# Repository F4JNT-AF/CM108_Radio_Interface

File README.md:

# [FR] (EN below)
## Description
Une interface basique USB entre une radio et un PC. Rien de révolutionnaire, j'ai essayé de mettre le maximum de composants traversants, avec deux exceptions assez techniques, le CM108 lui-même (pas trop le choix quand on veut faire une interface a base de CM108 :) ) et le connecteur USB-C (très pratique pour connecter en direct au téléphone sans OTG).

Avec cette interface, il est possible de faire de nombreux modes: packet, SSTV, RTTY, Rattlegram (COFDMTV), FT8 ... la seule limite étant ce que votre PC peut faire et la bande passante du transfo audio (il devrait être possible de ponter le transfo pour faire du packet en 9600 bauds sur les radios qui peuvent).

Une EEPROM (93C46B) peut être montée et servir a stocker un nom personnalisé pour l'interface ainsi que des paramètres audio par défaut.

[Objet d'un atelier en Mars 2025 a l'ARA35](https://ara35.fr/ce-soir-la-on-a-fabrique-des-interfaces-modes-numeriques-au-radio-club-f4kio/)

## Pinout connecteur RJ45
Le connecteur vers la radio est un RJ45. Le pinout est:
1. Speaker radio
2. Micro radio
3. PTT
4. GND radio
5. GND radio
6. GND radio
7. GND radio
8. GND radio

## Configuration de l'EEPROM
Utiliser le fichier .cfg (optionnel: mettre un numéro de série) ou .hex avec [mon configurateur d'EEPROM pour CM108B](https://github.com/F4JNT-AF/CM108B_EEPROM_Manager).

## Note
Comme toutes les interfaces de ce type, elle est plutôt sensible aux retours RF, je conseille de mettre des ferrites, au moins sur le câble USB.

73, Axel F4JNT

# [EN]
## Description
A basic USB interface between a radio and a PC. Nothing groundbreaking, I tried to use the maximum number of through-hole components, with two exceptions that are tricky to solder, the CM108 itself (not much choice when your interface is CM108-based :) ) and the USB-C connector (very handy to connect).

With this interface, you can do a lot of modes such as packet, SSTV, RTTY, Rattlegram (COFDMTV), FT8 ... your only limits will be what your PC or phone can handle and the bandwidth of the audio transformer (it should be possible to do 9600 bauds packet on compatible radios by shunting the transformers)

An EEPROM (93C46B) can be populated and may store a custom device name and audio parameters.

[Did a kit + workshop at ARA35](https://ara35.fr/ce-soir-la-on-a-fabrique-des-interfaces-modes-numeriques-au-radio-club-f4kio/)

## RJ45 Pinout
Connector to radio is RJ45. Pinout:
1. Speaker radio
2. Mic radio
3. PTT
4. GND radio
5. GND radio
6. GND radio
7. GND radio
8. GND radio

## EEPROM configuration
Use the .cfg file (optional: put a serial number) or .hex file with [my CM108B EEPROM configurator](https://github.com/F4JNT-AF/CM108B_EEPROM_Manager).

## Note
Note: As all interfaces of this type, it is vulnerable to RF feedback, I'd advise to at least add some ferrites to USB cable.

73, Axel F4JNT

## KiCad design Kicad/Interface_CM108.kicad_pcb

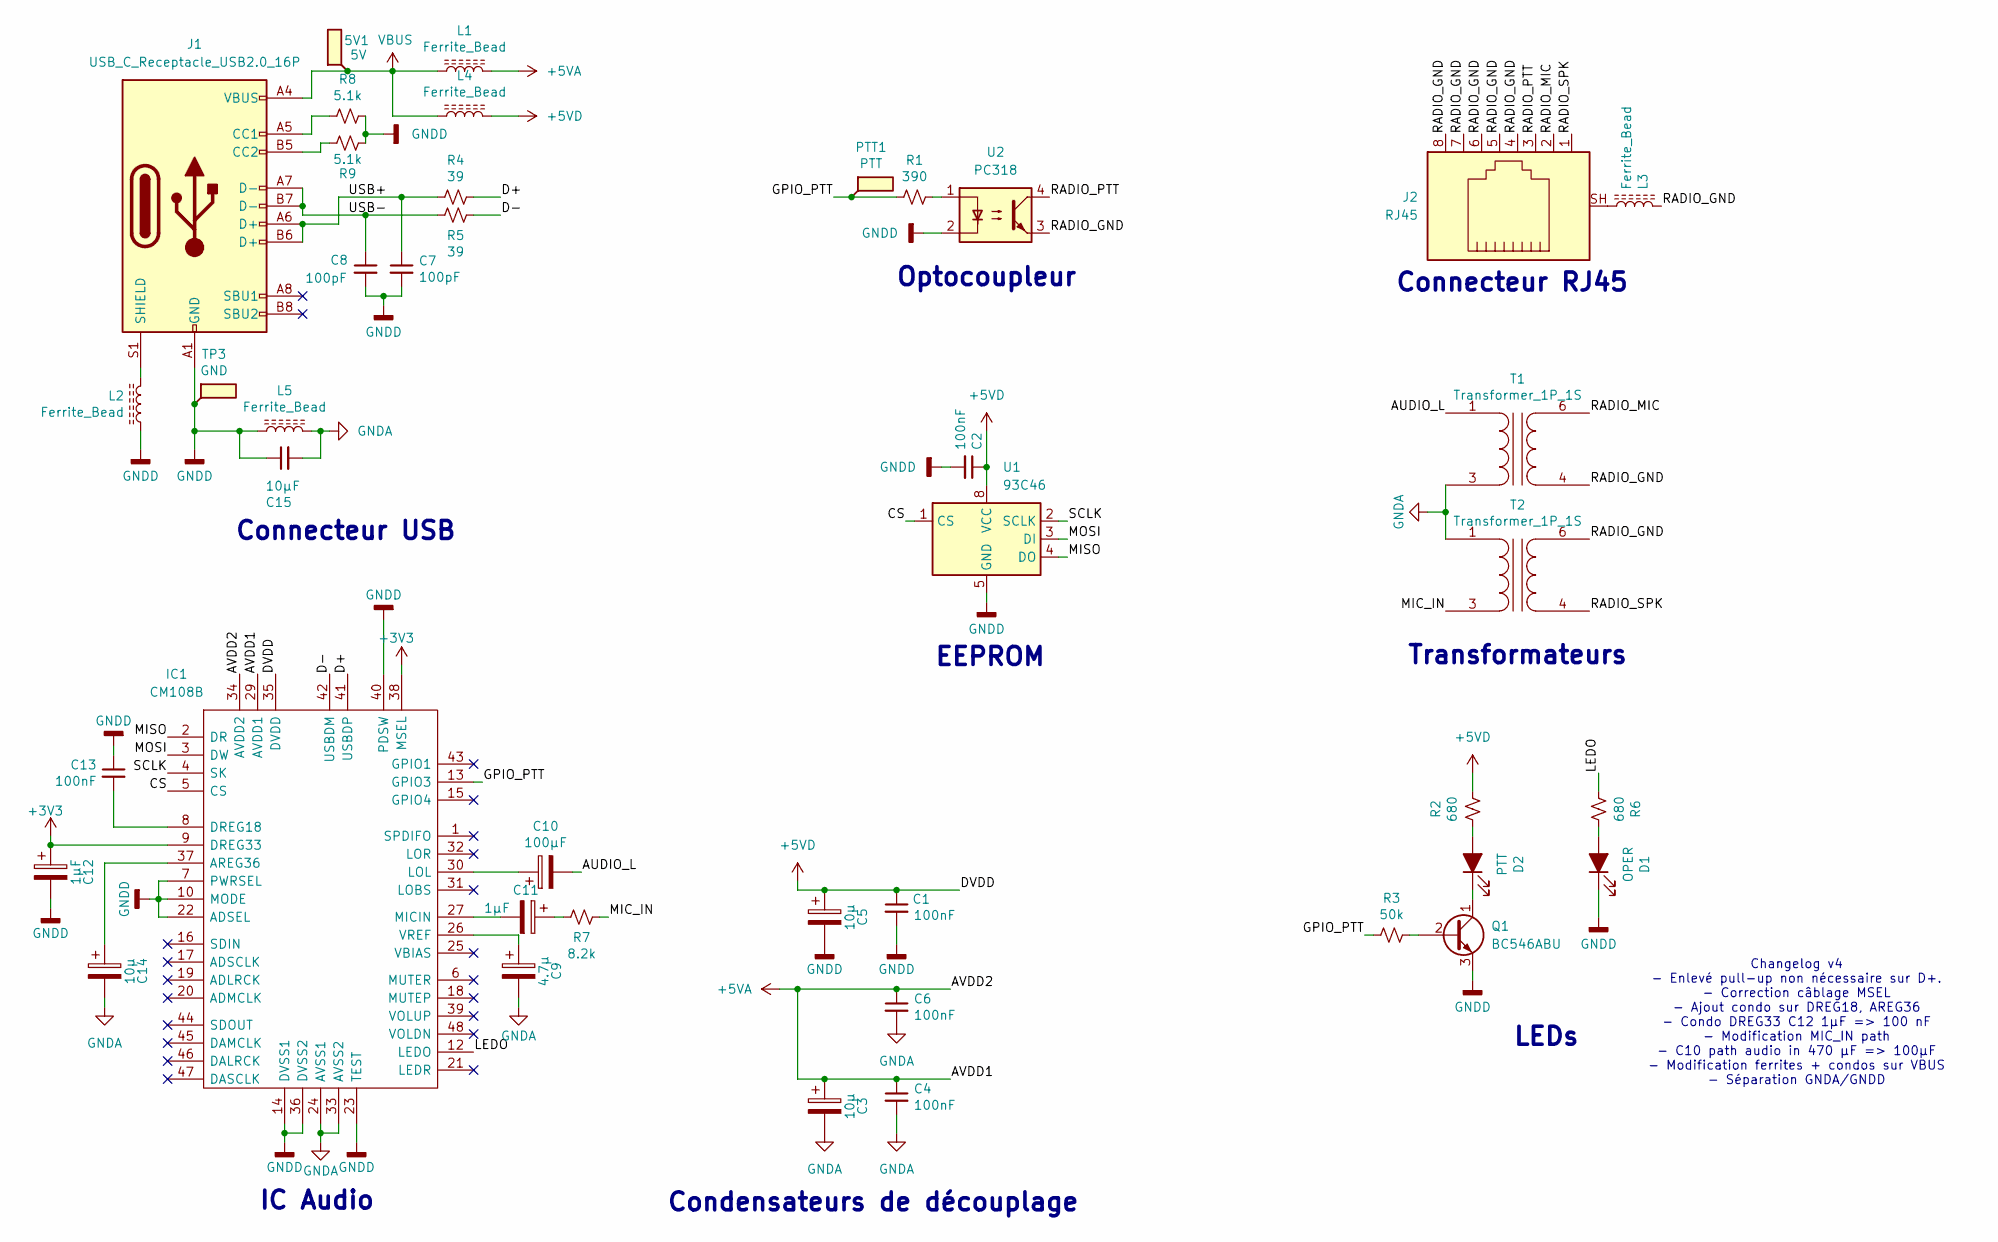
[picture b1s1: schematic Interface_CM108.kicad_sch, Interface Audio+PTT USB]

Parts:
5V1: 5V; TestPoint_Pad_D1.0mm
C1, C2, C4, C6, C13: 100nF; C_Disc_D3.8mm_W2.6mm_P2.50mm
C3, C5, C14: 10µ; CP_Radial_D5.0mm_P2.00mm
C7, C8: 100pF; C_Disc_D5.0mm_W2.5mm_P5.00mm
C9: 4.7µ; CP_Radial_D4.0mm_P1.50mm
C10: 100μF; CP_Radial_D5.0mm_P2.00mm
C11, C12: 1µF; CP_Radial_D5.0mm_P2.00mm
C15: 10µF; C_Disc_D3.8mm_W2.6mm_P2.50mm
D1: OPER; LED_D3.0mm
D2: PTT; LED_D3.0mm
IC1: CM108B; LQFP-48_7x7mm_P0.5mm
J1: USB_C_Receptacle_USB2.0_16P; USB_C_Receptacle_GCT_USB4105-xx-A_16P_TopMnt_Horizontal
J2: RJ45; RJ45_Ninigi_GE
L1, L2, L3, L4, L5: Ferrite_Bead; L_1210_3225Metric
PTT1: PTT; TestPoint_Pad_D1.0mm
Q1: BC546ABU; TO-92
R1: 390; R_Axial_DIN0207_L6.3mm_D2.5mm_P10.16mm_Horizontal
R2, R6: 680; R_Axial_DIN0207_L6.3mm_D2.5mm_P10.16mm_Horizontal
R3: 50k; R_Axial_DIN0207_L6.3mm_D2.5mm_P10.16mm_Horizontal
R4, R5: 39; R_Axial_DIN0207_L6.3mm_D2.5mm_P10.16mm_Horizontal
R7: 8.2k; R_Axial_DIN0207_L6.3mm_D2.5mm_P10.16mm_Horizontal
R8, R9: 5.1k; R_Axial_DIN0207_L6.3mm_D2.5mm_P10.16mm_Horizontal
T1, T2: Transformer_1P_1S; SMLP5001
TP3: GND; TestPoint_Pad_D1.0mm
U1: 93C46; DIP-8_W7.62mm
U2: PC318; DIP-4_W7.62mm

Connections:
+3V3: C12.1, IC1.9 (DREG33), IC1.38 (MSEL)
+5VA: C3.1, C4.1, C6.1, IC1.29 (AVDD1), IC1.34 (AVDD2), L1.2
+5VD: C1.1, C2.1, C5.1, IC1.35 (DVDD), L4.2, R2.1, U1.8 (VCC)
/AUDIO_L: C10.2, T1.1 (AA)
/CS: IC1.5 (CS), U1.1 (CS)
/D+: IC1.41 (USBDP), R4.1
/D-: IC1.42 (USBDM), R5.1
/GPIO_PTT: IC1.13 (GPIO3), PTT1.1, R1.2, R3.2; also elsewhere on the board
/LEDO: IC1.12 (LEDO), R6.2
/MIC_IN: R7.1, T2.3 (AB)
/MISO: IC1.2 (DR), U1.4 (DO)
/MOSI: IC1.3 (DW), U1.3 (DI)
/RADIO_GND: J2.4, J2.5, J2.6, J2.7, J2.8, L3.2, T1.4 (SA), T2.6 (SB), U2.3
/RADIO_MIC: J2.2, T1.6 (SB)
/RADIO_PTT: J2.3, U2.4
/RADIO_SPK: J2.1, T2.4 (SA)
/SCLK: IC1.4 (SK), U1.2 (SCLK)
/USB+: C7.1, J1.A6 (D+), J1.B6 (D+), R4.2
/USB-: C8.1, J1.A7 (D-), J1.B7 (D-), R5.2
GNDA: C3.2, C4.2, C6.2, C9.2, C14.2, C15.2, IC1.24 (AVSS1), IC1.33 (AVSS2), L5.2, T1.3 (AB), T2.1 (AA)
GNDD: C1.2, C2.2, C5.2, C7.2, C8.2, C12.2, C13.1, C15.1, D1.1 (K), IC1.7 (PWRSEL), IC1.10 (MODE), IC1.14 (DVSS1), IC1.22 (ADSEL), IC1.23 (TEST), IC1.36 (DVSS2), IC1.40 (PDSW), J1.A1 (GND), J1.A12 (GND), J1.B1 (GND), J1.B12 (GND), L2.1, L5.1, Q1.3 (E), R8.1, R9.1, TP3.1, U1.5 (GND), U2.2; also elsewhere on the board
unnamed: C11.1, R7.2
unnamed: D1.2 (A), R6.1
unnamed: D2.2 (A), R2.2
unnamed: D2.1 (K), Q1.1 (C)
unnamed: C14.1, IC1.37 (AREG36)
unnamed: C13.2, IC1.8 (DREG18)
unnamed: C10.1, IC1.30 (LOL)
unnamed: C11.2, IC1.27 (MICIN)
unnamed: C9.1, IC1.26 (VREF)
unnamed: J1.A5 (CC1), R8.2
unnamed: J1.B5 (CC2), R9.2
unnamed: J1.S1 (SHIELD), L2.2
unnamed: J2.SH, L3.1
unnamed: Q1.2 (B), R3.1
unnamed: R1.1, U2.1
VBUS: 5V1.1, J1.A4 (VBUS), J1.A9 (VBUS), J1.B4 (VBUS), J1.B9 (VBUS), L1.1, L4.1; also elsewhere on the board

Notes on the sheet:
EEPROM
Transformateurs
Connecteur USB
LEDs
Connecteur RJ45
Changelog v4 - Enlevé pull-up non nécessaire sur D+. - Correction câblage MSEL - Ajout condo sur DREG18, AREG36 - Condo DREG33 C12 1µF => 100 nF - Modification MIC_IN path - C10 path audio in 470 µF => 100µF - Modification ferrites + condos sur VBUS - Séparation GNDA/GNDD
Condensateurs de découplage
IC Audio
Optocoupleur

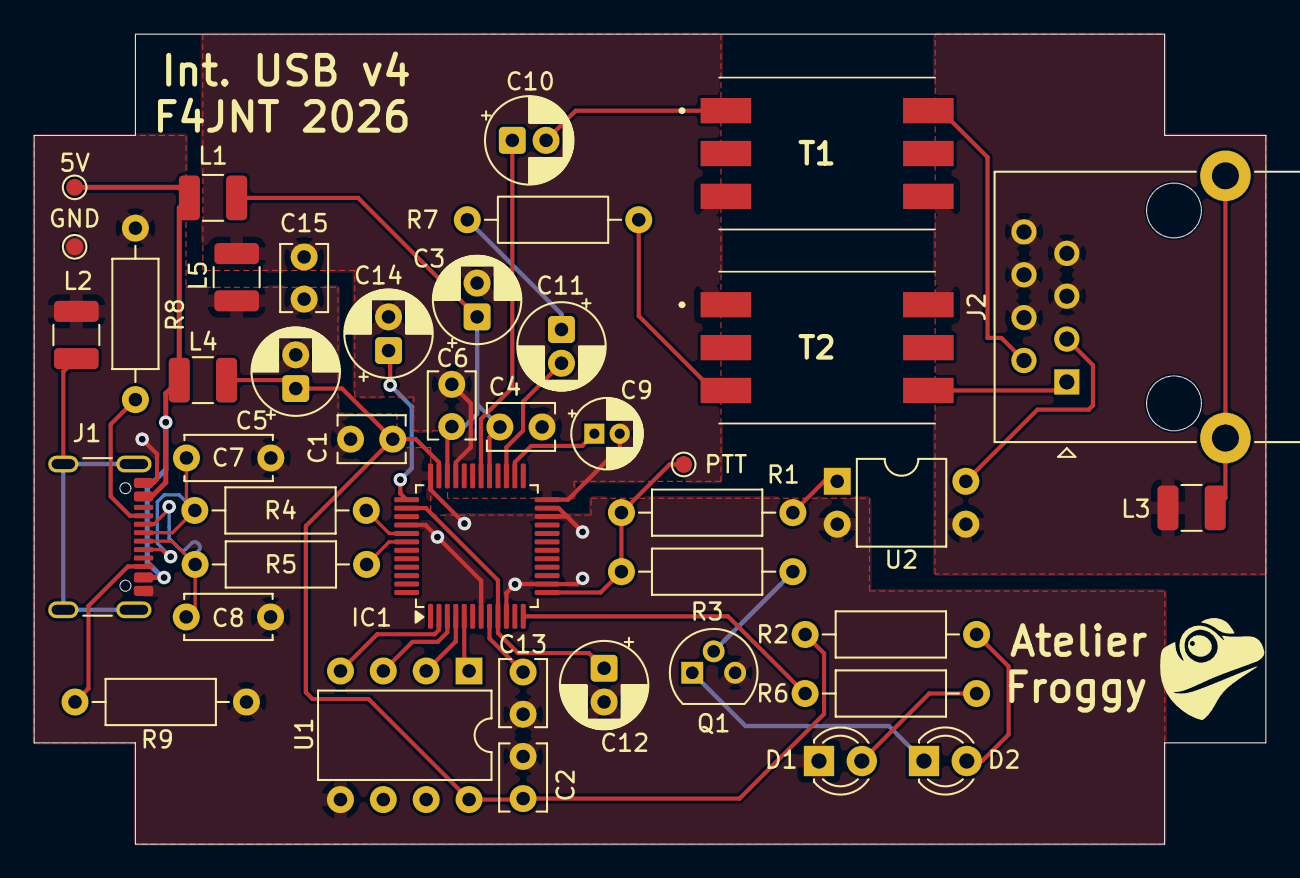
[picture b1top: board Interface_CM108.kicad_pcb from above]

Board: 2 copper layers, 73.0 x 48.0 mm, 42 parts (0 on the bottom side), 37 nets.

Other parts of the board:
5V: 5V; TestPoint_Pad_D1.0mm
GND: GND; TestPoint_Pad_D1.0mm
PTT: PTT; TestPoint_Pad_D1.0mm

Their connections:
/GPIO_PTT: PTT.1 (1_1); also elsewhere on the board
GNDD: GND.1 (1_1); also elsewhere on the board
VBUS: 5V.1 (1_1); also elsewhere on the board

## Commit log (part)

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2025-12-10 Initial Commit
    V3 as assembled in March
2025-12-10 Add README content
    Added detailed descriptions and pinout information for the USB interface between a radio and a PC in both French and English.
